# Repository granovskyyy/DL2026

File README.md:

# DL2026
Design Lab classes repository 
Project - IoT system based on ATMega328PB with all connectivity interfaces (I2C, SPI, UART etc) 
### FEATURES
The projects support various connectivity protocols such as: 
- UART
- I2C
- SPI
- 1-WIRE
- Outputs (7seg display)  
Software functions:
- UART connectivity and displaying counter of 7-seg display as well as data obtained from the sensors.
### HARDWARE
- ATMega328PB - microcontroller  
- BMP280 - Pressure sensor 
- DS18B20 – temperature probe 
- PL2303 - UART connectivity (in schematic is FT232RL used due to KiCad avaibality) 
- 3.3V voltage regulators 
- Capacitors (100n ceramic and 10uF electrolytic) 
- Resistors (4,7K to pullup, 220 for 7seg)
### SCHEMATIC

### PCB LAYOUT

### PCB MODEL

### PROJECT STRUCTURES  
- /datasheets/-  Components datasheets 
- schematics/  -  Schematics and PCB designs 
- I2C-BMP280/  -  I2C examples with BMP280 
- Final Project – complete DL code with support for all protocols 
- README.md

### SOFTWARE
- KiCad
- AVR Microchip Studio
#### COMPILATION 
avr-gcc -mmcu=atmega328pb -Os -o main.elf source_file.c
avr-objcopy -O ihex main.elf main.hex
#### FLASH
avrdude -c usbasp -p m328pb -U flash:w:main.hex

NOTE- you can compile code via Makefile

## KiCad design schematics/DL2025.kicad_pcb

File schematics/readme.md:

KICad is required to open schematics

This custom circuit was designed to measure properties of the fluids or gases using sensors, which could be obtained by connecting to the board via USB to uart connection or serial port.

Overall structure of the project is:
    -> datasheets folder - contains datasheets of all the elements used in the project.
    It is: 
        sensors: 
            BMP280, 
            BS18B20, 
        usb to uart: 
            PL2303GS USB to Full UART IC, 
        ATmega328PB Xplained Mini board.
    -> I2C-BMP280 folder - containing base library of communicating with BMP280 sensors via I2C interface, which was helpful in process of writing custom firmware for the project case.
    -> schematics folder - containing Electric Schematic and PCB design of the circuit.
    -> Final Project folder - containing final versions of the software used to read and display the data from sensors.

Firmware was written in C to maintain high readability, modularity and speed of the code, as well as future development of the project.

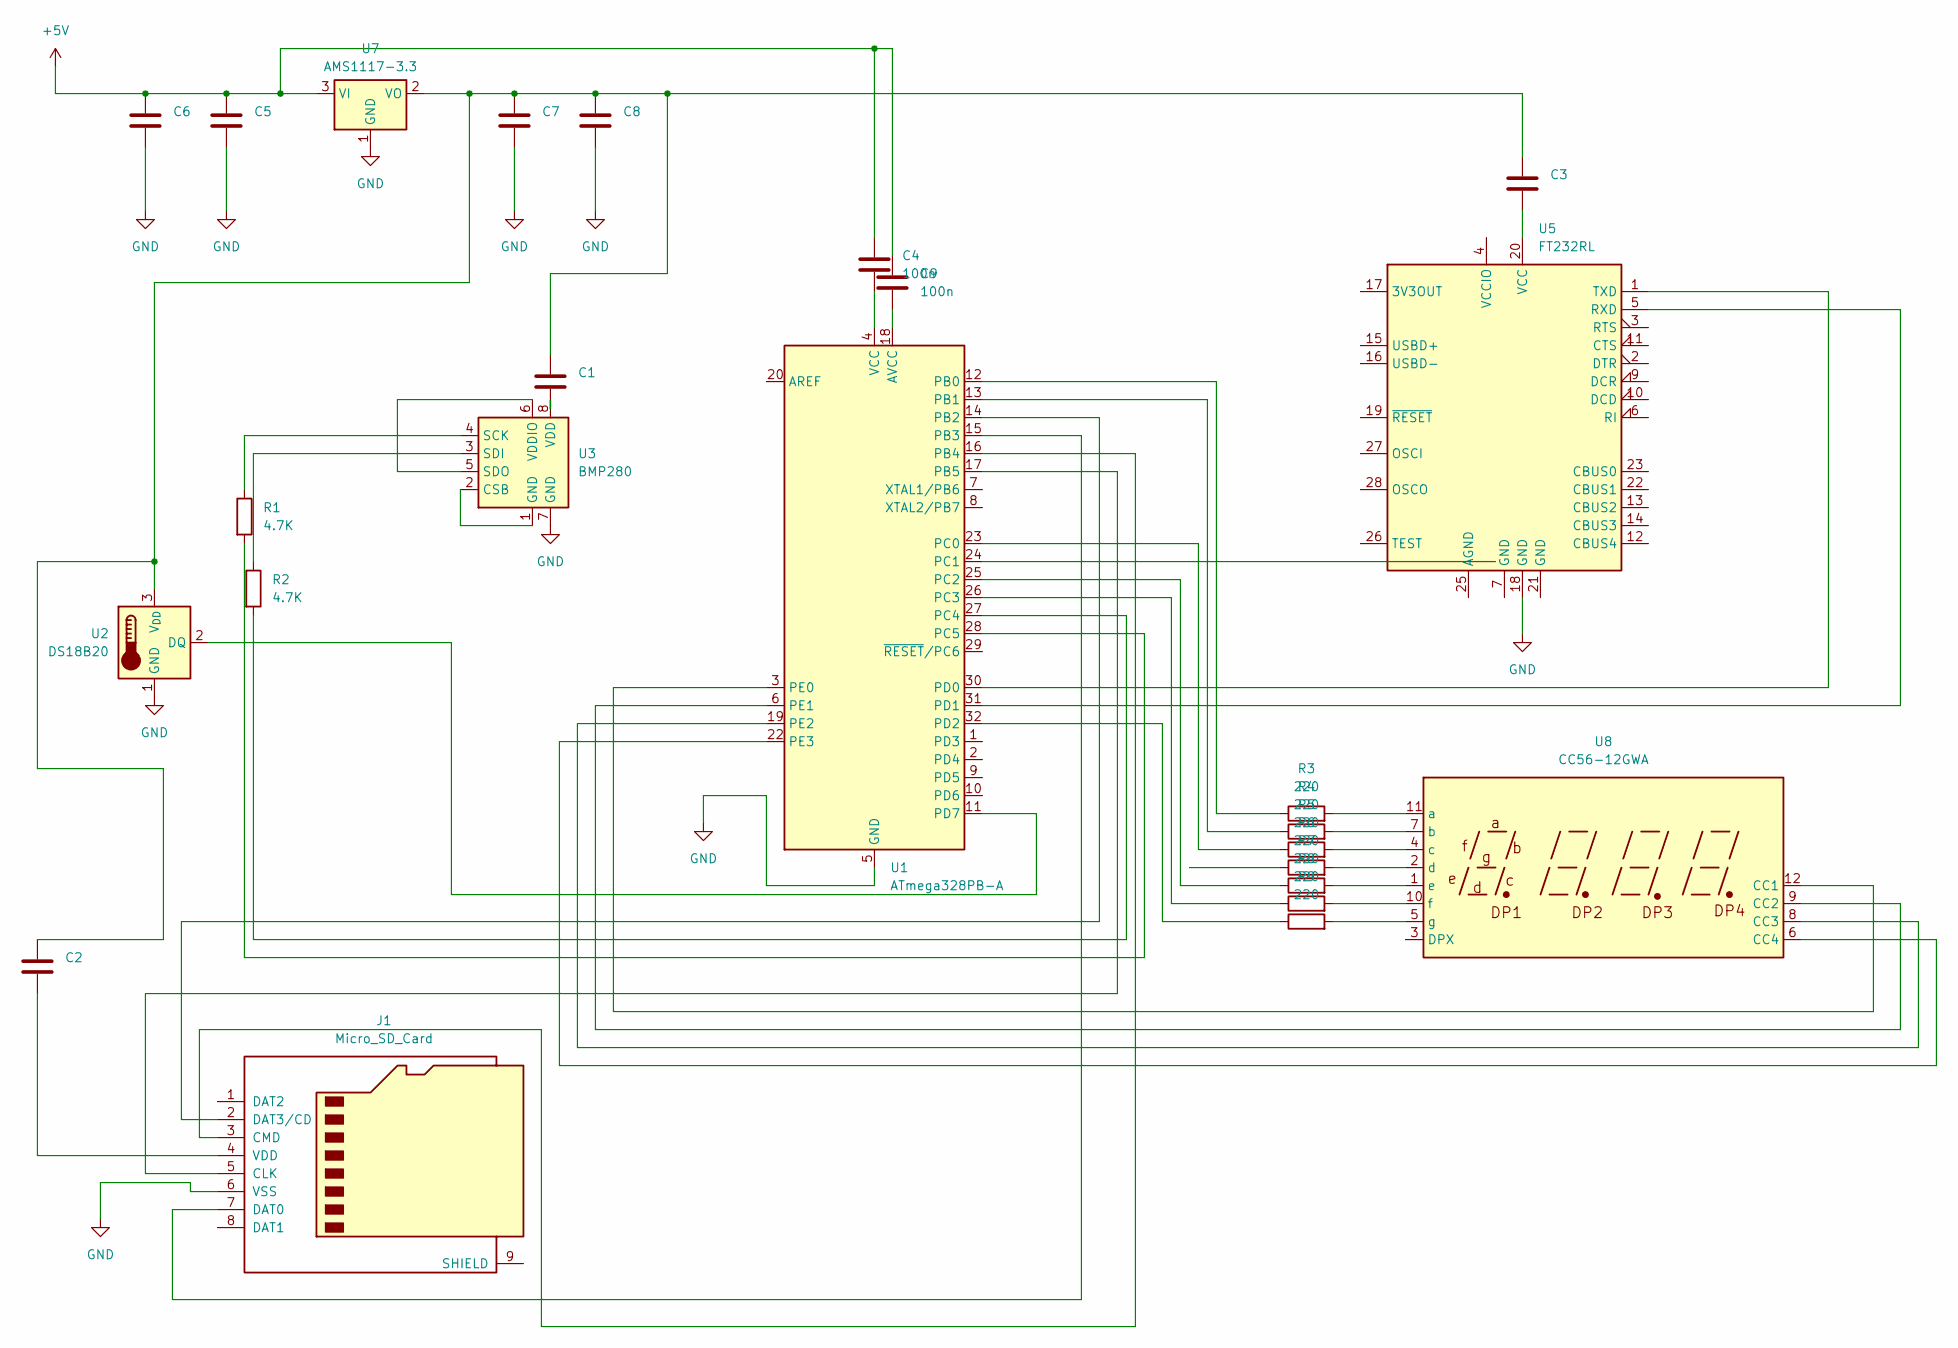
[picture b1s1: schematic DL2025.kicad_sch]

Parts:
C1, C2, C3, C4, C5, C7, C9: 100n; CP_Elec_4x3
C6, C8: 10u; CP_Radial_D4.0mm_P1.50mm
J1: Micro_SD_Card; PinHeader_1x09_P1.00mm_Horizontal
R1, R2: 4.7K; R_0508_1220Metric_Pad1.12x2.15mm_HandSolder
R3, R4, R5, R6, R7, R8, R9: 220; R_0508_1220Metric_Pad1.12x2.15mm_HandSolder
U1: ATmega328PB-A; TQFP-32_7x7mm_P0.8mm
U2: DS18B20; TO-92_Inline
U3: BMP280; Bosch_LGA-8_2x2.5mm_P0.65mm_ClockwisePinNumbering
U5: FT232RL; SSOP-28_5.3x10.2mm_P0.65mm
U7: AMS1117-3.3; SOT-223-3_TabPin2
U8: CC56-12GWA

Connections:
+5V: C4.1, C5.1, C6.1, C9.1, U7.3 (VI)
GND: C5.2, C6.2, C7.2, C8.2, J1.6 (VSS), U1.5 (GND), U1.21 (GND), U2.1 (GND), U3.7 (GND), U5.18 (GND), U7.1 (GND)
unnamed: J1.5 (CLK), U1.17 (PB5)
unnamed: J1.3 (CMD), U1.16 (PB4)
unnamed: J1.7 (DAT0), U1.15 (PB3)
unnamed: J1.2 (DAT3/CD), U1.14 (PB2)
unnamed: C2.2, J1.4 (VDD)
unnamed: C9.2, U1.18 (AVCC)
unnamed: R3.1, U1.12 (PB0)
unnamed: R4.1, U1.13 (PB1)
unnamed: R5.1, U1.23 (PC0)
unnamed: R6.1, U1.24 (PC1)
unnamed: R7.1, U1.25 (PC2)
unnamed: R8.1, U1.26 (PC3)
unnamed: R2.2, U1.27 (PC4)
unnamed: R1.2, U1.28 (PC5)
unnamed: U1.30 (PD0), U5.1 (TXD)
unnamed: U1.31 (PD1), U5.5 (RXD)
unnamed: R9.1, U1.32 (PD2)
unnamed: U1.11 (PD7), U2.2 (DQ)
unnamed: U1.3 (PE0), U8.12 (CC1)
unnamed: U1.6 (PE1), U8.9 (CC2)
unnamed: U1.19 (PE2), U8.8 (CC3)
unnamed: U1.22 (PE3), U8.6 (CC4)
unnamed: C4.2, U1.4 (VCC)
unnamed: C1.1, C2.1, C3.1, C7.1, C8.1, U2.3 (V_{DD}), U7.2 (VO)
unnamed: U3.1 (GND), U3.2 (CSB)
unnamed: R1.1, U3.4 (SCK)
unnamed: R2.1, U3.3 (SDI)
unnamed: U3.5 (SDO), U3.6 (VDDIO)
unnamed: C1.2, U3.8 (VDD)
unnamed: C3.2, U5.20 (VCC)
unnamed: R3.2, U8.11 (a)
unnamed: R4.2, U8.7 (b)
unnamed: R5.2, U8.4 (c)
unnamed: R6.2, U8.2 (d)
unnamed: R7.2, U8.1 (e)
unnamed: R8.2, U8.10 (f)
unnamed: R9.2, U8.5 (g)

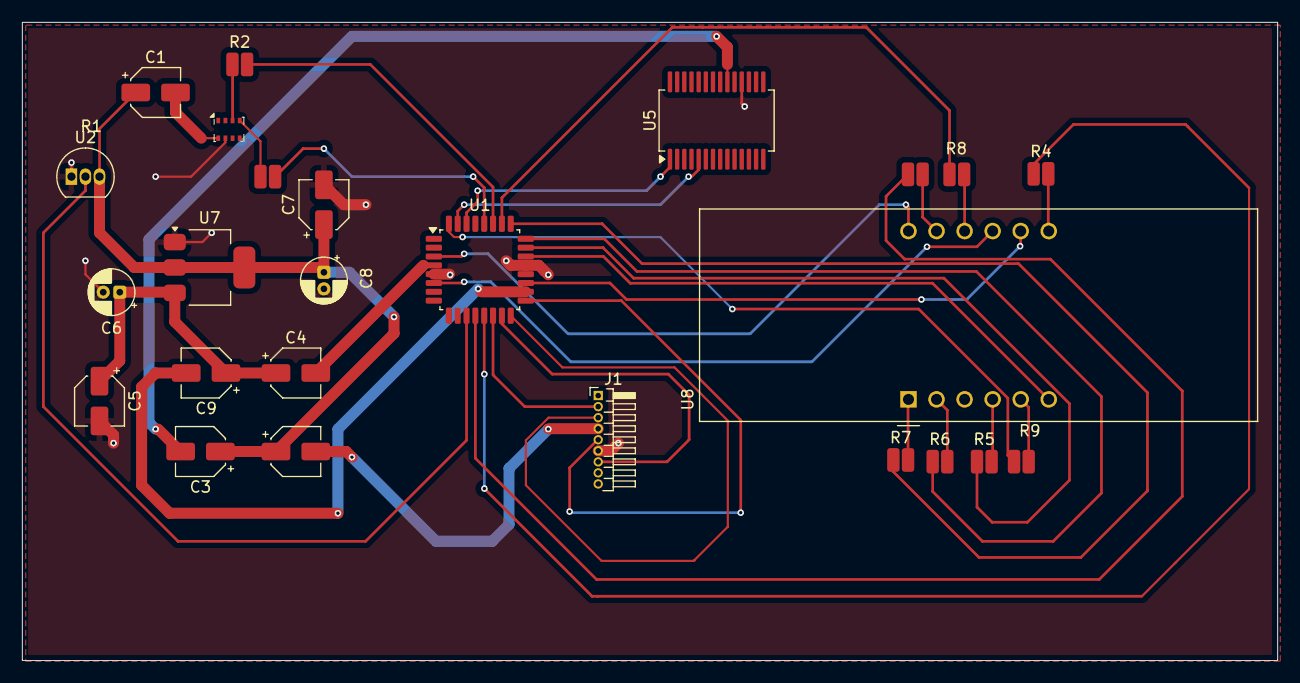
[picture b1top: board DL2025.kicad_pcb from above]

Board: 2 copper layers, 113.7 x 57.8 mm, 25 parts (0 on the bottom side), 39 nets.

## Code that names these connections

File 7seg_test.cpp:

#include <avr/io.h>
#include <util/delay.h>

// digit_map[n] = bity g f e d c b a (1 = segment ma ?wieci? logicznie)
const uint8_t digit_map[10] = {
	0b00111111, // 0
	0b00000110, // 1
	0b01011011, // 2
	0b01001111, // 3
	0b01100110, // 4
	0b01101101, // 5
	0b01111101, // 6
	0b00000111, // 7
	0b01111111, // 8
	0b01101111  // 9
};

// WSPÓLNA ANODA: segment ON = 0, OFF = 1
void set_segments(uint8_t seg)
{
	// a -> PB0 (bit0)
	if (seg & (1<<0)) PORTB &= ~(1<<PB0);   // ON -> 0
	else              PORTB |=  (1<<PB0);   // OFF -> 1

	// b -> PB1 (bit1)
	if (seg & (1<<1)) PORTB &= ~(1<<PB1);
	else              PORTB |=  (1<<PB1);

	// c -> PC0 (bit2)
	if (seg & (1<<2)) PORTC &= ~(1<<PC0);
	else              PORTC |=  (1<<PC0);

	// d -> PC1 (bit3)
	if (seg & (1<<3)) PORTC &= ~(1<<PC1);
	else              PORTC |=  (1<<PC1);

	// e -> PC2 (bit4)
	if (seg & (1<<4)) PORTC &= ~(1<<PC2);
	else              PORTC |=  (1<<PC2);

	// f -> PC3 (bit5)
	if (seg & (1<<5)) PORTC &= ~(1<<PC3);
	else              PORTC |=  (1<<PC3);

	// g -> PD2 (bit6)
	if (seg & (1<<6)) PORTD &= ~(1<<PD2);
	else              PORTD |=  (1<<PD2);
}

// Wy?wietlenie jednej cyfry na danej pozycji (0..3)
void show_digit(uint8_t position, uint8_t value)
{
	// wy??cz wszystkie cyfry (anody w 1 = OFF, je?li aktywne stanem niskim)
	PORTE |= (1<<PE0)|(1<<PE1)|(1<<PE2)|(1<<PE3);

	// ustaw odpowiednie segmenty (wspólna anoda: segment ON = 0)
	set_segments(digit_map[value]);

	// w??cz wybran? cyfr? (anoda w 0 = ON)
	switch (position) {
		case 0: PORTE &= ~(1<<PE0); break; // cyfra tysi?cy
		case 1: PORTE &= ~(1<<PE1); break; // cyfra setek
		case 2: PORTE &= ~(1<<PE2); break; // cyfra dziesi?tek
		case 3: PORTE &= ~(1<<PE3); break; // cyfra jedno?ci
	}

	_delay_ms(3);
}

int main(void)
{
	// segmenty jako wyj?cia
	DDRB |= (1<<PB0)|(1<<PB1);
	DDRC |= (1<<PC0)|(1<<PC1)|(1<<PC2)|(1<<PC3);
	DDRD |= (1<<PD2);

	// wybór cyfr na 7-segu jako wyj?cia
	DDRE |= (1<<PE0)|(1<<PE1)|(1<<PE2)|(1<<PE3);

	// chcemy stale wy?wietla? 1234
	uint8_t digits[4] = {1, 2, 3, 4};

	while (1) {
		// multipleksowanie czterech cyfr
 		for (uint8_t i = 0; i < 4; i++) {
 			show_digit(i, digits[i]);
 		}
	}
}

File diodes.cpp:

#include <avr/io.h>
#define F_CPU 16000000UL
#include <util/delay.h>

#define rx PD0
#define tx PD1
#define I2C1 PC4
#define I2C2 PC5
#define SPI PC1


int main(void)
{
	DDRD |= (1 << rx) | (1 << tx);
	DDRC |= (1 << I2C1) | (1 << I2C2) | (1 << SPI);


    while (1) 
    {
		PORTD|= (1 << rx) |  (1 << tx);
		PORTC|= (1 << I2C1) | (1 << I2C2) | (1 << SPI);
		
		_delay_ms(500);
		
		PORTD &= ~((1 << rx) |  (1 << tx));
		PORTC &= ~((1 << I2C1) | (1 << I2C2) | (1 << SPI));
		
		_delay_ms(500);
    }
}

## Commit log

2025-10-14 7 seg datasheet
2025-10-15 block diagram of circuit
2025-11-04 kicad scheme of circuit
2025-11-04 Update readme with KICad requirement
    Added requirement for KICad to open schematics.
2025-11-04 added 7seg_test.cpp
2025-11-17 Add UART functionality and display digit control
    Implement UART communication and 7-segment display control
2025-11-19 PCB board
2025-12-02 Updated schematics, just one AMS1117
2025-12-02 Added new schematics: atmega328pb, uart
2025-12-02 Updated schematics, added LCD_DP -> PC3 connection
2025-12-03 Added helpful library for BMP280
2025-12-03 Added working firmware for BMP280 and sonda
2025-12-03 updated PCB schematic
2025-12-03 updated schematic, added capacitors
2025-12-15 Create Final Project
    Final touch to the project
2025-12-15 Create main.cpp
    Final touch to the project
2025-12-15 Upload of the whole project
    Final touch to the project
2025-12-16 Update README with PCB layout image
    Added PCB layout image to README.
2025-12-16 Enhance README with schematic and PCB details
    Added schematic, PCB layout, and PCB model sections with images.
2025-12-16 Fix formatting of section headers in README.md
2025-12-16 Enhance README with project details and instructions
    Added features, hardware details, project structure, and software compilation instructions to the README.
2025-12-16 updated schematics
2026-01-15 added labview project
2026-01-20 documentation upload
